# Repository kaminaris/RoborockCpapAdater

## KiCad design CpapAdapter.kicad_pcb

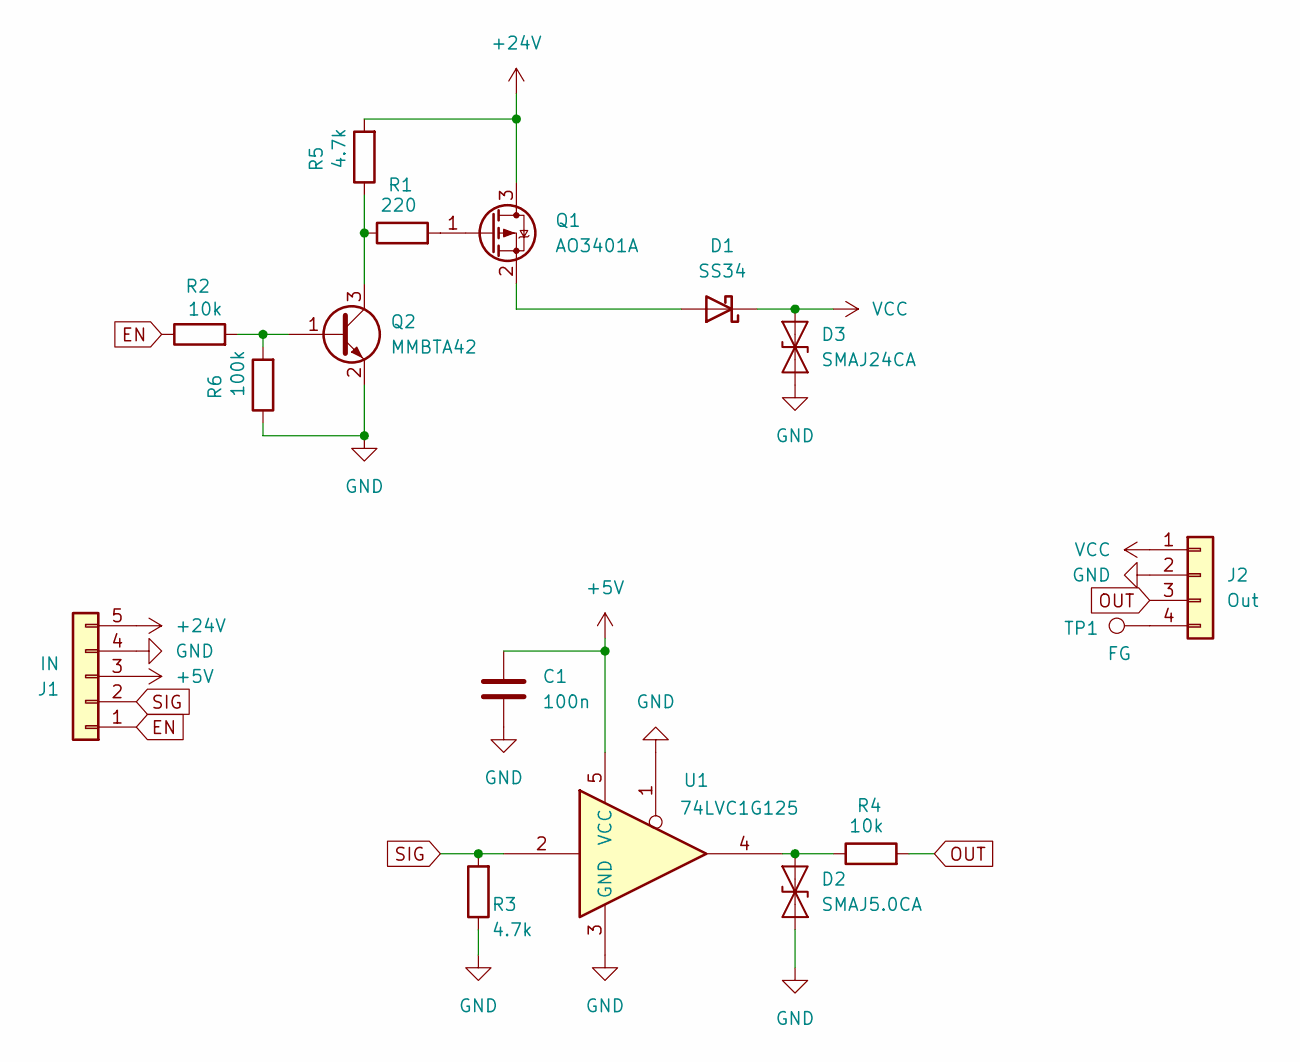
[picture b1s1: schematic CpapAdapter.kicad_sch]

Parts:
C1: 100n; C_0603_1608Metric_Pad1.08x0.95mm_HandSolder
D1: SS34; D_SMB_Handsoldering
D2: SMAJ5.0CA; D_SMA
D3: SMAJ24CA; D_SMA
J1: IN; PinHeader_1x05_P2.54mm_Horizontal
J2: Out; PinHeader_1x04_P2.54mm_Horizontal
Q1: AO3401A; SOT-23
Q2: MMBTA42; SOT-23
R1: 220; R_0603_1608Metric_Pad0.98x0.95mm_HandSolder
R2, R4: 10k; R_0603_1608Metric_Pad0.98x0.95mm_HandSolder
R3, R5: 4.7k; R_0603_1608Metric_Pad0.98x0.95mm_HandSolder
R6: 100k; R_0603_1608Metric_Pad0.98x0.95mm_HandSolder
TP1: FG; TestPoint_THTPad_D2.0mm_Drill1.0mm
U1: 74LVC1G125; SOT-23-5

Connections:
+5V: C1.1, J1.3, U1.5 (VCC)
+24V: J1.5, Q1.3 (D), R5.2
EN: J1.1, R2.1
GND: C1.2, D2.2 (A2), D3.2 (A2), J1.4, J2.2, Q2.2 (E), R3.1, R6.1, U1.1, U1.3 (GND)
unnamed: D1.2 (A), Q1.2 (S)
unnamed: D2.1 (A1), R4.1, U1.4
unnamed: J2.4, TP1.1
unnamed: Q1.1 (G), R1.2
unnamed: Q2.1 (B), R2.2, R6.2
unnamed: Q2.3 (C), R1.1, R5.1
OUT: J2.3, R4.2
SIG: J1.2, R3.2, U1.2
VCC: D1.1 (K), D3.1 (A1), J2.1

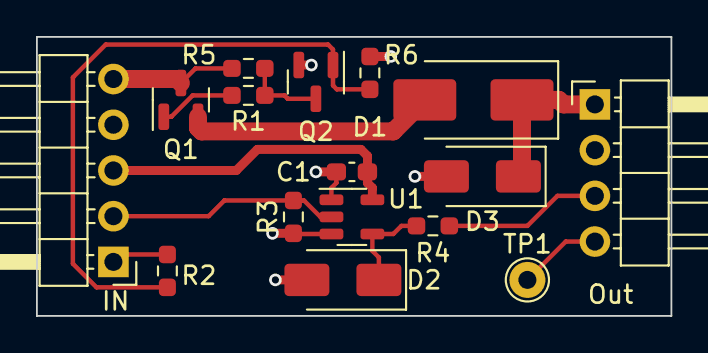
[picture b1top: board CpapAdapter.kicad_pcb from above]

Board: 2 copper layers, 35.2 x 15.5 mm, 16 parts (0 on the bottom side), 13 nets.

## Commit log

2024-02-05 initial
